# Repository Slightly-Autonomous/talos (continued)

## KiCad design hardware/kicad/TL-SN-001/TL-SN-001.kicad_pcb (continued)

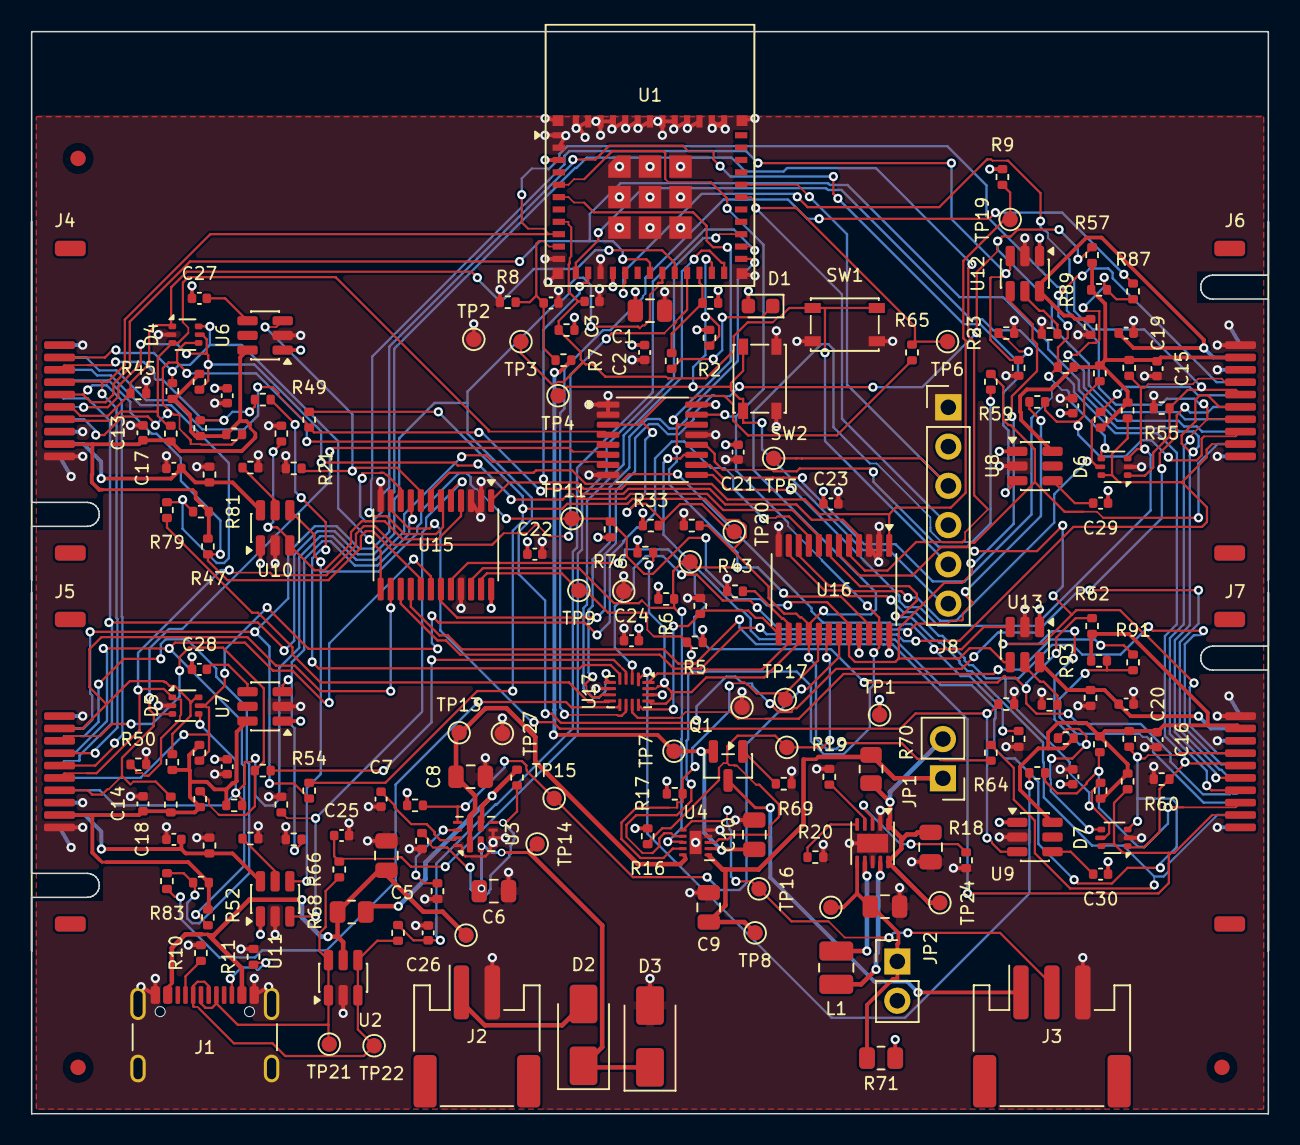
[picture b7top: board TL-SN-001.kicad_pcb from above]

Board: 4 copper layers, 80.0 x 70.0 mm, 195 parts (0 on the bottom side), 120 nets.

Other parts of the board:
FID1, FID2, FID3: fiducial; Fiducial_1mm_Mask2mm

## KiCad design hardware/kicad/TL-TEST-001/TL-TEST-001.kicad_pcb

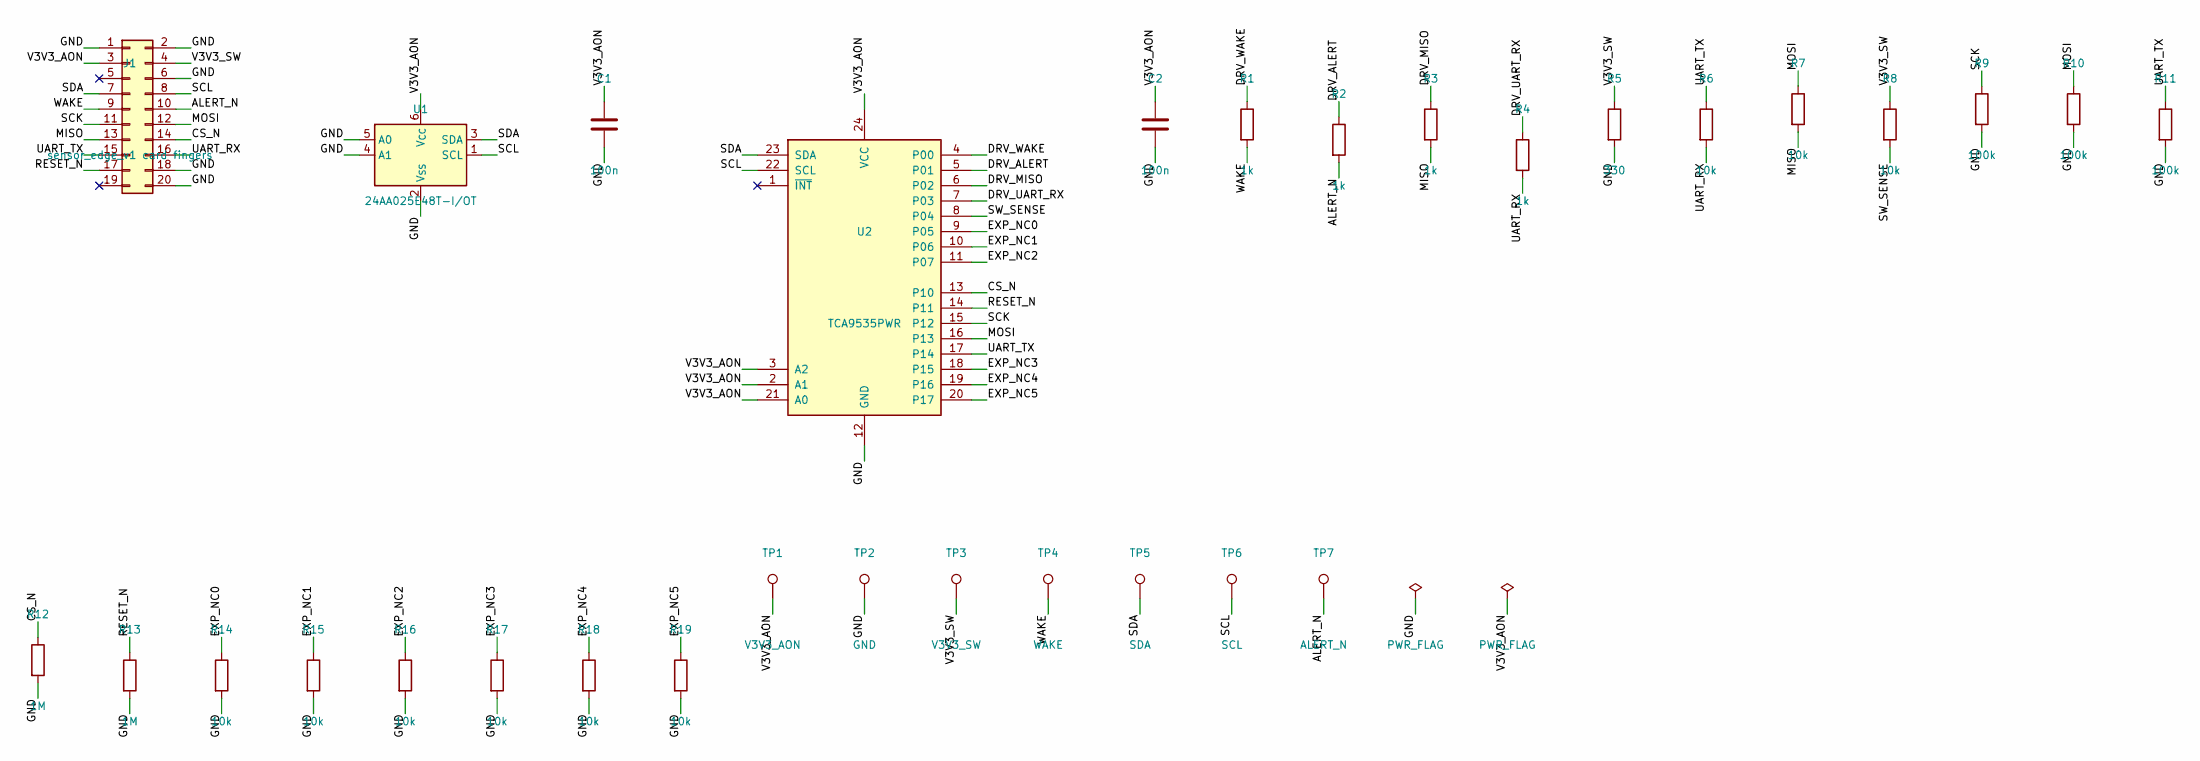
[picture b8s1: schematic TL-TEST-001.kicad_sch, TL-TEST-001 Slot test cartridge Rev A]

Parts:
C1, C2: 100n; C_0402_1005Metric
J1: sensor_edge_v1 card fingers; CardEdge_sensor_edge_v1_2x10_P0.8mm
R1, R2, R3, R4: 1k; R_0402_1005Metric
R5: 330; R_0402_1005Metric
R6, R7, R8, R14, R15, R16, R17, R18, R19: 10k; R_0402_1005Metric
R9, R10, R11: 100k; R_0402_1005Metric
R12, R13: 1M; R_0402_1005Metric
TP1: V3V3_AON; TestPoint_Pad_D1.0mm
TP2: GND; TestPoint_Pad_D1.0mm
TP3: V3V3_SW; TestPoint_Pad_D1.0mm
TP4: WAKE; TestPoint_Pad_D1.0mm
TP5: SDA; TestPoint_Pad_D1.0mm
TP6: SCL; TestPoint_Pad_D1.0mm
TP7: ALERT_N; TestPoint_Pad_D1.0mm
U1: 24AA025E48T-I/OT; SOT-23-6
U2: TCA9535PWR; TSSOP-24_4.4x7.8mm_P0.65mm

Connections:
/ALERT_N: J1.10, R2.2, TP7.1
/CS_N: J1.14, R12.1, U2.13 (P10)
/DRV_ALERT: R2.1, U2.5 (P01)
/DRV_MISO: R3.1, U2.6 (P02)
/DRV_UART_RX: R4.1, U2.7 (P03)
/DRV_WAKE: R1.1, U2.4 (P00)
/EXP_NC0: R14.1, U2.9 (P05)
/EXP_NC1: R15.1, U2.10 (P06)
/EXP_NC2: R16.1, U2.11 (P07)
/EXP_NC3: R17.1, U2.18 (P15)
/EXP_NC4: R18.1, U2.19 (P16)
/EXP_NC5: R19.1, U2.20 (P17)
/GND: C1.2, C2.2, J1.1, J1.2, J1.6, J1.18, J1.20, R5.2, R9.2, R10.2, R11.2, R12.2, R13.2, R14.2, R15.2, R16.2, R17.2, R18.2, R19.2, TP2.1, U1.2 (V_{SS}), U1.4 (A1), U1.5 (A0), U2.12 (GND)
/MISO: J1.13, R3.2, R7.2
/MOSI: J1.12, R7.1, R10.1, U2.16 (P13)
/RESET_N: J1.17, R13.1, U2.14 (P11)
/SCK: J1.11, R9.1, U2.15 (P12)
/SCL: J1.8, TP6.1, U1.1 (SCL), U2.22 (SCL)
/SDA: J1.7, TP5.1, U1.3 (SDA), U2.23 (SDA)
/SW_SENSE: R8.2, U2.8 (P04)
/UART_RX: J1.16, R4.2, R6.2
/UART_TX: J1.15, R6.1, R11.1, U2.17 (P14)
/V3V3_AON: C1.1, C2.1, J1.3, TP1.1, U1.6 (V_{CC}), U2.2 (A1), U2.3 (A2), U2.21 (A0), U2.24 (VCC)
/V3V3_SW: J1.4, R5.1, R8.1, TP3.1
/WAKE: J1.9, R1.2, TP4.1

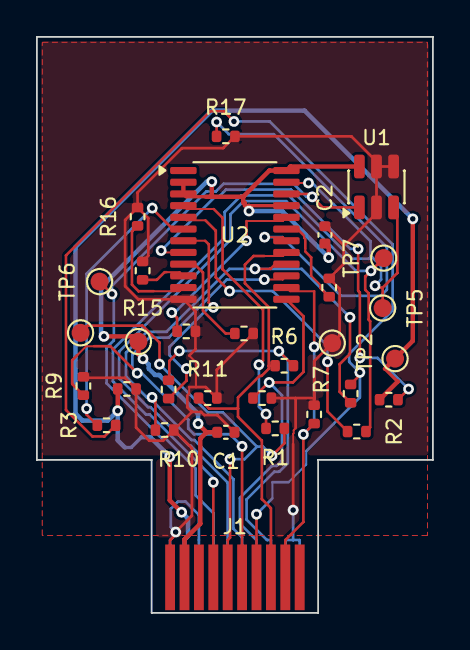
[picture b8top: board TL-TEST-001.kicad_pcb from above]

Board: 2 copper layers, 22.0 x 32.0 mm, 31 parts (0 on the bottom side), 25 nets.

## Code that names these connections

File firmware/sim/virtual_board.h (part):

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  std::function<void()> on_write;  // a pin may have changed: update what it drives
  // Every pin that has ever driven a 1 as an output (catches config-before-output).
  std::uint16_t ever_driven_high = 0;
  // Fault: pins held high from outside (a solder bridge to V3V3) whatever drives them.
  std::uint16_t bridged_high = 0;
  // INT (open drain, active low): asserted while an input pin differs from the
  // value it had when its port was last read; reading the port releases it.
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  bool aon_on(std::uint8_t slot) const;  // TPS22917 ON level (1M pull-down when not driven)
  bool sw_on(std::uint8_t slot) const;   // 1M pull-down when not driven
  // Line level at the card for RESET_N / CS_N (pulled up to the slot's AON).
  bool reset_n(std::uint8_t slot) const;
  bool cs_n(std::uint8_t slot) const;

 private:
  bool expander_pin(const ExpanderPin& p, bool undriven) const;
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};

// TL-SN-002 Rev A (ADR 0019): one TCA9535 for eight lamps and PIR_PWR, built-in
// sensors on the root bus, direct GPIO inputs (tamper, USER, USB_PRESENT).
// Mirrors firmware/esp_idf/main/board_tl_sn_002.h (pull resistors included).
class Sn002Board {
 public:
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  // Lamp lit (its expander pin an output driven low; 2.2k to 3V3).
  bool lamp(Lamp l) const;
  bool sensor_led(std::uint8_t slot) const;
  std::uint32_t pir_power_cycles = 0;  // PIR_PWR high -> low transitions

 private:
  bool pin_lit(const ExpanderPin& p) const;
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  Sn002Board& sn002() { return *sn002_; }
  bool is_sn002() const { return sn002_.has_value(); }
  // Drive a sensor's output line: on TL-SN-002 the PIR line only follows while
  // PIR_PWR is on; everything else is a plain GPIO level.
  void set_line(std::uint8_t line, bool level);
  BoardIo& board_io() { return *board_io_; }
  bool has_board_io() const { return board_io_.has_value(); }
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
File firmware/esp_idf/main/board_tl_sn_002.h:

// Board support for TL-SN-002 Rev A, the self-contained sensor node (ADR 0019).
//
// PROVISIONAL: every number here waits for the TL-SN-002 schematic review and
// the bench. GPIO capabilities follow the ESP32-H2-MINI-1 datasheet v1.6 and the
// ESP32-H2 Series datasheet v1.3 §2.2: only LP GPIO8-14 can wake the chip from
// deep sleep, so the five wake sources sit on GPIO10-14, all ACTIVE HIGH, and
// one ext1 ANY_HIGH mask covers them (the TMAG5273 INT_N keeps its SN74AUP1G04
// inverter, owner decision 2026-11-21, so HD-004's per-pin polarity is not needed).
// Keep this table and contracts/manifests/boards/sensor_node_v2.yaml in
// agreement (tools/dbg/tests/test_contracts.py checks the two).
//
// Built-in sensors are fixed "slots" (SlotWiring::fixed_module): no mux, no ID
// EEPROMs, no presence lines, no per-slot rails except PIR_PWR.
//   slot 0  MAG  TMAG5273B2  0x22  INT_N -> SN74AUP1G04 -> GPIO10 (MAG_WAKE)
//   slot 1  VIB  LIS2DW12    0x19  INT1 push-pull active high -> GPIO11 (SA0 high, CS high)
//   slot 2  PIR  PIR223D-S0  -     digital out, 1M pull-down -> GPIO12; rail = EXP P10 PIR_PWR
//   slot 3  ENV  SHT40-AD1B  0x44  no interrupt
// TMAG5273B2: the letter is the address variant (B = 0x22, SLYS045C Table 6-2)
// and the digit the range (2 = +/-133/266 mT). Was the A2 (0x35) until it went
// out of stock at JLCPCB (2026-11-24, HD-045); same die, pinout and range.
#pragma once

#include "firmware/portable/hal.h"
#include "firmware/portable/modules.h"

namespace talos::fw::board::sn002 {

inline constexpr const char* kBoardName = "TL-SN-002";
inline constexpr int kI2cSda = 2;  // root I2C, 4.7k pull-ups to 3V3
inline constexpr int kI2cScl = 3;
inline constexpr int kBatterySenseAdc = 1;  // ADC1_CH0: VBAT after reverse protection, 4.7M/4.7M
// VBUS through 100k/100k: high = USB powers the node (TPS2116 prefers IN1 = VBUS).
// GPIO4 is a digital pad (not LP): read while awake only, never a wake source.
inline constexpr std::uint8_t kUsbPresent = 4;
// Status LED (STAT): strap pin, active low, 10k pull-up. Driven only after boot.
inline constexpr std::uint8_t kStatusLed = 8;
// BOOT button: strap at reset (download mode, ROM), service-mode toggle after boot.
inline constexpr std::uint8_t kBootButton = 9;
// Five LP wake lines, all active high (ext1 ANY_HIGH).
inline constexpr std::uint8_t kMagWake = 10;  // TMAG5273B2 INT_N through SN74AUP1G04
inline constexpr std::uint8_t kAccInt = 11;   // LIS2DW12 INT1, push-pull active high
inline constexpr std::uint8_t kPirOut = 12;   // PIR223D-S0 output, 1M pull-down
// SW4 lid + SW5 battery door in series to GND, 1M pull-up + 10 nF.
inline constexpr std::uint8_t kTamper = 13;
inline constexpr std::uint8_t kUserButton = 14;  // to 3V3, 100k pull-down
// GPIO0, 5, 22, 25: spare (GPIO0 on a test pad). GPIO23/24: U0RXD/U0TXD on the
// Tag-Connect recovery pads. GPIO26/27: USB Serial/JTAG (flash, console, debug).

// TCA9535 at 0x20 (A0-A2 GND). INT not connected: its one input (P11) is read
// when the tamper line (GPIO13, a wake source) says the loop opened.
//   P00 LED_LINK_N  P01 LED_MAG_N  P02 LED_VIB_N  P03 LED_PIR_N
//   P04 LED_ENV_N   P05 LED_TAMP_N P06 LED_BATT_N P07 LED_FLT_N   (active low, 2.2k to 3V3)
//   P10 PIR_PWR (high = PIR powered through an RC filter; the expander holds it in deep sleep)
//   P11 TAMPER_DOOR in (4.7M pull-up, SW5 to GND: high = battery door open, HD-049)
//   P12-P17 unused: outputs driven low.
inline constexpr std::uint8_t kExp = 0x20;
inline constexpr std::uint8_t kPirPowerPin = 8;     // P10
inline constexpr std::uint8_t kBatteryDoorPin = 9;  // P11

inline BoardSupport tl_sn_002() {
  BoardSupport b;
  b.name = kBoardName;
  b.mux_address = 0;  // no mux: the built-in sensors share the root bus
  auto fixed = [](std::uint8_t wake, ModuleCode code) {
    SlotWiring w;
    w.present = true;
    w.wake_line = wake;
    w.fixed_module = static_cast<std::uint16_t>(code);
    return w;
  };
  b.slots[0] = fixed(kMagWake, ModuleCode::kTmag5273A2);
  b.slots[1] = fixed(kAccInt, ModuleCode::kLis2dw12);
  b.slots[2] = fixed(kPirOut, ModuleCode::kPir223d);
  b.slots[3] = fixed(0xFF, ModuleCode::kSht40);
  b.slot_io[2].aon_enable = {kExp, kPirPowerPin};  // PIR_PWR is the PIR "slot"'s only rail
  // Per-sensor activity lamps reuse the slot-LED policy (L-03).
  b.slot_led_n[0] = {kExp, 1};  // MAG
  b.slot_led_n[1] = {kExp, 2};  // VIB
  b.slot_led_n[2] = {kExp, 3};  // PIR
  b.slot_led_n[3] = {kExp, 4};  // ENV
  b.lamp_n[static_cast<std::size_t>(Lamp::kLink)] = {kExp, 0};
  b.lamp_n[static_cast<std::size_t>(Lamp::kTamper)] = {kExp, 5};
  b.lamp_n[static_cast<std::size_t>(Lamp::kBattery)] = {kExp, 6};
  b.lamp_n[static_cast<std::size_t>(Lamp::kFault)] = {kExp, 7};
  b.unused_pins[0] = {kExp, 0xFC00};  // P12-P17
  b.battery_door = {kExp, kBatteryDoorPin};
  b.status_led_line = kStatusLed;
  b.service_button_line = kBootButton;
  b.tamper_line = kTamper;
  b.user_button_line = kUserButton;
  b.usb_present_line = kUsbPresent;
  // 2 x AA Li-FeS2 (Energizer L91 class), primary: ~3.6 V fresh (open circuit),
  // ~3.0 V plateau under load, then a knee. Thresholds are pair voltages UNDER
  // LOAD (after a radio burst). PROVISIONAL. Low = 2.2 V (1.10 V/cell) from
  // hardware/results/power-budget-sn2.md: it keeps the TPS63900 input >= 1.8 V
  // during an 18 dBm TX burst at -40 C. Below it the node reports low battery
  // (BATT lamp, PowerMode::kLowPower) and caps TX power at +10 dBm (about half
  // the burst current of +18 dBm, ~11 dB less link margin). PROVISIONAL (HD-043).
  b.primary_battery = true;
  b.battery_low_mv = 2200;
  b.battery_critical_mv = 2000;  // 1.0 V/cell loaded: the 1.8 V regulator floor is close
  b.battery_ota_min_mv = 2600;   // an OTA is minutes of radio: only on healthy cells
  // The loaded reading is noisy (burst length, temperature): leaving low power or
  // critical needs 100 mV above the threshold, so the mode can't flap per heartbeat.
  b.battery_hysteresis_mv = 100;
  b.tx_power_dbm = 18;
  b.tx_power_low_battery_dbm = 10;
  // Owner 2026-11-22: deep sleep between reports by default (<= 2 s event
  // latency); the hub can switch a node to kSleepyChild or kAlwaysOn per device.
  b.power_profile = PowerProfile::kDeepSleep;
  // Module admission budgets (provisional). Battery: card-equivalent draw only,
  // the board baseline is in the power budget. USB: TPS63900 0.4 A x 3.3 V minus
  // the radio TX burst, as TL-SN-001.
  b.battery_sustained_mw = 15;
  b.usb_sustained_mw = 800;
  // The USB-C port stays reachable from outside the closed enclosure (owner,
  // 2026-11-22): the console is read-only while the lid is closed, and the
  // firmware lamps (STAT included) light only with the lid open or in service
  // mode, so a cable or power bank on the outside port changes and reveals nothing.
  // The hardware PWR lamp on VBUS stays: it only says USB power is present.
  b.console_lock = ConsoleLock::kLidClosed;
  b.lamp_gate = LampGate::kLidOpen;
  return b;
}

}  // namespace talos::fw::board::sn002
